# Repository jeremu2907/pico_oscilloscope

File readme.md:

https://github.com/user-attachments/assets/dc531678-6600-4c17-865a-9ecb72ba17ac

https://github.com/user-attachments/assets/cd0efd30-149d-468c-a42a-c6fa3a5c8240

https://github.com/user-attachments/assets/f2d84a0b-0583-4837-9c11-803d82c9e2e8

https://github.com/user-attachments/assets/791f4eb1-17fd-4e78-958c-5dc652bf3b7a

# Version 2

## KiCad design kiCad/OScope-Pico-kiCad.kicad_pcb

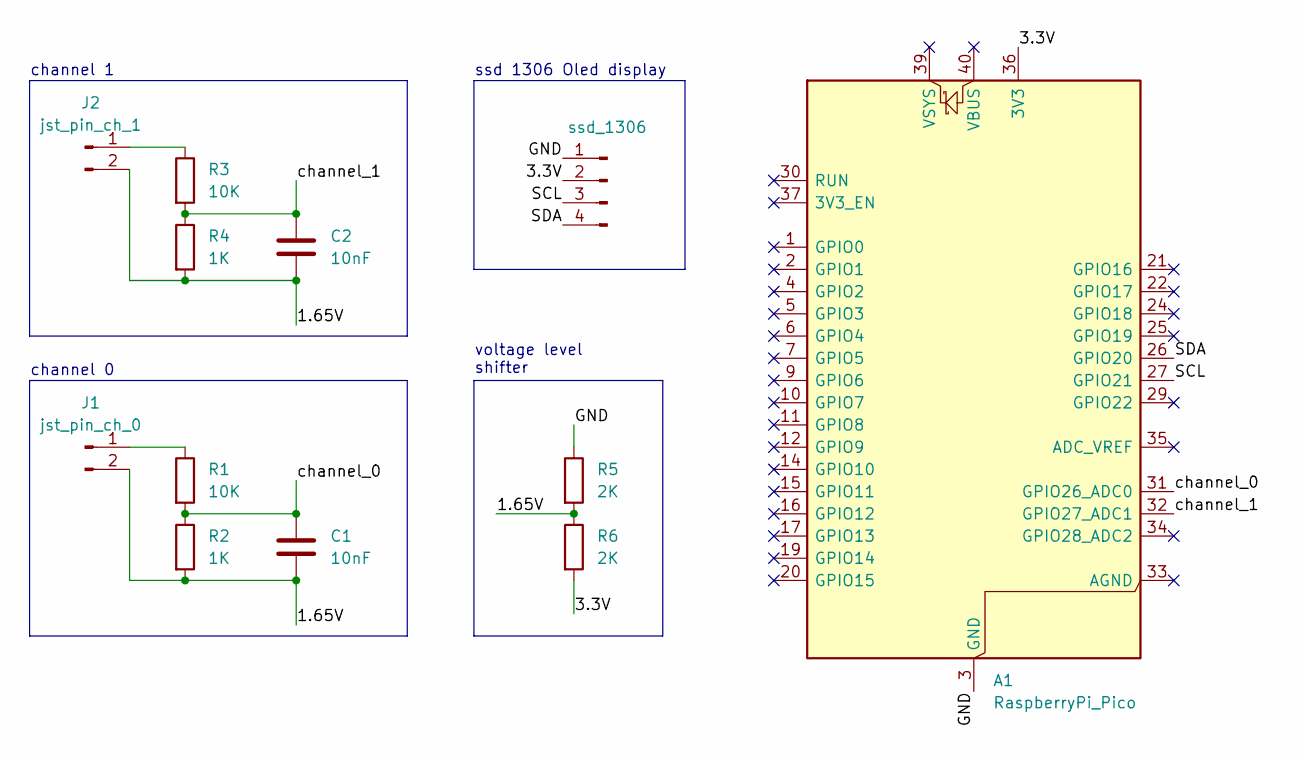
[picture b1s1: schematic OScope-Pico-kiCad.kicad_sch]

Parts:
A1: RaspberryPi_Pico; RaspberryPi_Pico_Common_Unspecified
C1, C2: 10nF; C_Disc_D3.0mm_W1.6mm_P2.50mm
J1: jst_pin_ch_0; JST_EH_B2B-EH-A_1x02_P2.50mm_Vertical
J2: jst_pin_ch_1; JST_EH_B2B-EH-A_1x02_P2.50mm_Vertical
R1, R3: 10K; R_Axial_DIN0204_L3.6mm_D1.6mm_P5.08mm_Horizontal
R2, R4: 1K; R_Axial_DIN0204_L3.6mm_D1.6mm_P5.08mm_Horizontal
R5, R6: 2K; R_Axial_DIN0204_L3.6mm_D1.6mm_P5.08mm_Horizontal
ssd_1306: ssd_1306; JST_EH_B4B-EH-A_1x04_P2.50mm_Vertical

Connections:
/1.65V: C1.2, C2.2, J1.2, J2.2, R2.2, R4.2, R5.2, R6.1
/3.3V: A1.36 (3V3), R6.2, ssd_1306.2
/GND: A1.3 (GND), A1.8 (GND), A1.13 (GND), A1.18 (GND), A1.23 (GND), A1.28 (GND), A1.38 (GND), R5.1, ssd_1306.1
/SCL: A1.27 (GPIO21), ssd_1306.3
/SDA: A1.26 (GPIO20), ssd_1306.4
/channel_0: A1.31 (GPIO26_ADC0), C1.1, R1.2, R2.1
/channel_1: A1.32 (GPIO27_ADC1), C2.1, R3.2, R4.1
unnamed: J1.1, R1.1
unnamed: J2.1, R3.1

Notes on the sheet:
ssd 1306 Oled display
voltage level shifter
channel 0
channel 1

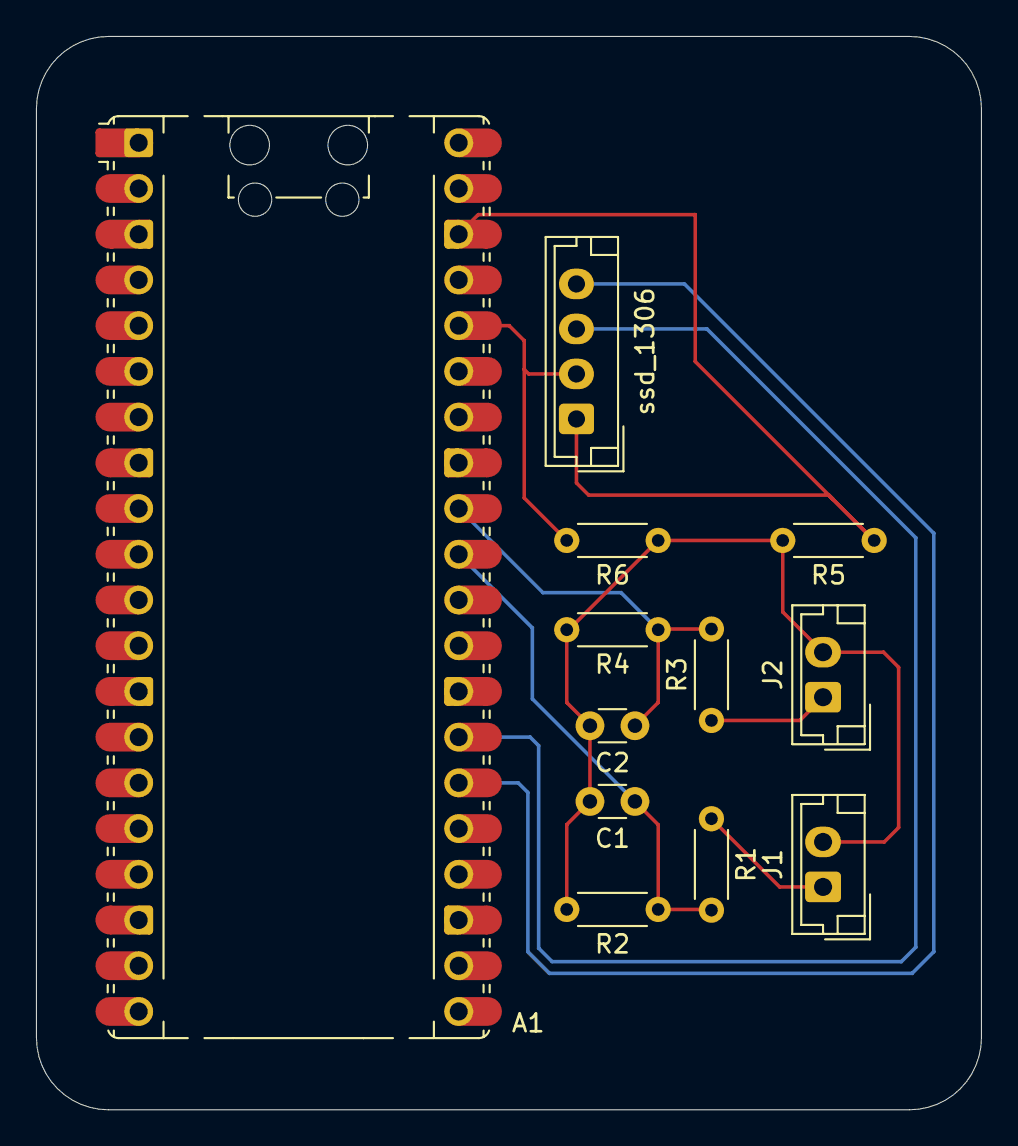
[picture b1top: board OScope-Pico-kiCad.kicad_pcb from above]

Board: 2 copper layers, 52.5 x 59.6 mm, 12 parts (0 on the bottom side), 9 nets.

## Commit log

2025-11-29 working
2025-11-29 added oled screen
2025-11-29 added visual
2025-11-30 Update readme with new image links
    Added additional image links to the readme.
2025-11-30 Update README with new asset links
    Added additional asset links to the README.
2025-12-05 Modified
2025-12-06 ki cad
2025-12-06 removed magic number and calibrated
2025-12-09 done
